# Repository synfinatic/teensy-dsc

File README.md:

# TeensyDSC: WiFi enabled Digital Setting Circles

## Important Note

As of Nov 16, 2014 I've been able to order a PCB from OSHPark using the 
[Simple-DSC](https://github.com/synfinatic/teensy-dsc/tree/simple-dsc/eagle)
design and with the latest code from 
[master](https://github.com/synfinatic/teensy-dsc/commit/1c4c6b0b567ba3cc21cd7ba83029384eee6130e7).
I seem to have a working solution using SkySafari Pro on my iPad with 
[US Digital S2-2500](http://www.usdigital.com/products/encoders/incremental/rotary/shaft/S2)
10,000 step optical encoders.

For more information, please see the [TeensyDSC Wiki](https://github.com/synfinatic/teensy-dsc/wiki)

There is also this thread on [CloudyNights](http://www.cloudynights.com/topic/482436-yet-another-diy-digital-setting-circles-project-teensydsc/)

## Basic Features
I wanted to do my own digital setting circles (DSC) for my 
[Apertura AD12](http://www.opticsmart.com/telescopes/dobsonian-telescopes/apertura-ad12-dobsonian-reflector-telescope.html).
The main goals were:

 * Tested to support 40,000 resolution via quadurature decoding using [US Digital S2-10000-250-IE-D-D encoders](http://usdigital.com/products/encoders/incremental/rotary/shaft/S2)
 * Should support resolutions in excess of 100K
 * Built in WiFi access point to allow wirelessly interfacing to an Apple iPad or Android tablet
 * Supporting at least [SkySafari Plus/Pro](http://www.skysafariastronomy.com/)
 * Powered via USB connection or external 7-24V battery source
 * Using industry standard RJ45 connection to encoders
 * Open source software & PCB design (GPLv3)
    * PCB Design done in [Eagle PCB](http://www.cadsoftusa.com/eagle-pcb-design-software/?language=en)
    * PCB's available from [OshPark](http://www.oshpark.com)
 * Small 2"x3"x1" enclosure
 * Inexpensive!  All the components should be available for < $100.

That will be version 1.0.  Future versions will hopefully support other features,
but for now that will be enough for it to work for me.

## Why Teensy 3.1
Why the [Teensy 3.1](http://pjrc.com/store/teensy31.html) and not Arduino?

 * It is *much* faster then the Arduino Uno or Mega (32bit 72Mhz CPU vs 16bit 16Mhz)
 * Small footprint and only costs $20!
 * Runs at 3.3V, but handles 5V just fine which simplifies talking to WiFi chipsets and encoders
 * It supports interrupts on all digital pins which allows for higher resolution encoders
 * Has 3 hardware serial ports which allows interfacing with GoTo hardware, etc
 * More memory & flash allows for a lot more features

## Required Libraries & Software
TeensyDSC requires some additional Arduino libraries to compile/run:

 * [Arduino IDE v1.6.x](http://arduino.cc/en/Main/Software)
 * [Teensyduino](http://pjrc.com/teensy/td_download.html) - Teensy addon for the Arduino IDE

The following libraries are included with the TeensyDSC source code, but you
will need to import them into the Arduino IDE:

 * [AnySerial](https://github.com/synfinatic/AnySerial) - Serial port abstraction layer for Arduino
 * [WiFi_Shield](https://github.com/synfinatic/WiFi_Shield) - Customized to use AnySerial
 * [Flash](https://github.com/mikalhart/Flash) - Easy access to EEPROM flash memory

## Supported DSC Software
Please note that I have limited access to software, so this may not be a
complete list.  If you have tested TeensyDSC with some software, I'd love
to hear if it worked or not.  If it did not work, hopefully we can work
together to make it work!

 * SkySafari (OSX, iOS)  
   * Scope Type: Basic Encoder System
   * For "Encoder Steps per Revolution" click "Get Automatically"

## Similar Projects
There are a bunch of similar projects to TeensyDSC which you should be aware of:

 * [mrosseel/arduino-dsc](https://github.com/mrosseel/arduino-dsc)
 * [mdw123/arduino-dsc](https://github.com/mdw123/arduino-dsc)
 * [Arduino Bluetooth DSC](http://orlygoingthirty.blogspot.com/2012/01/arduino-bluetooth-digital-setting.html)
 * [Mike Fulbright's Arduino DSC](http://msfastro.net/articles/arduinodsc/)

## Similar Commercial Products
There are two commercial products which shares many of the same features of TeensyDSC:

 * [Astro Devices Nexus](http://www.astrodevices.com/products/Nexus/Nexus.html)
 * [Dave Ek's Setting Circles](http://eksfiles.net/digital-setting-circles/)

## DSC to WiFi adapters
These commercial products connect your DSC adapter (Sky Commander, etc) to Sky Safari:

 * [Southern Stars/Orion SkyFi](http://www.southernstars.com/products/skyfi/)
 * [Astro Devices Nexus-S](http://www.astrodevices.com/products/NexusS/NexusS.html)

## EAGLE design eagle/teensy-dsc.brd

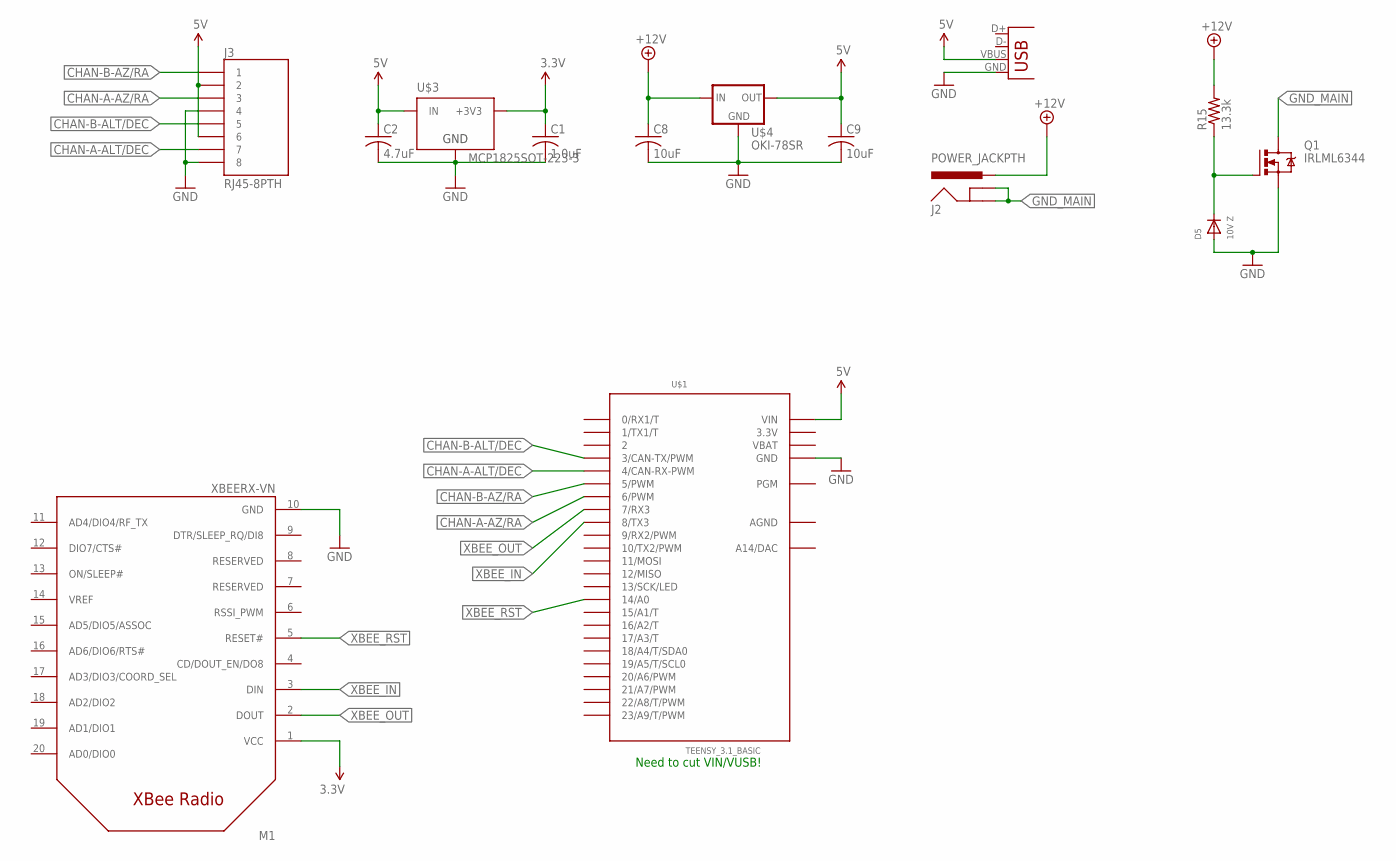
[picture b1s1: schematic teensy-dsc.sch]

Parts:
C1: 1.0uF; C0805
C2: 4.7uF; C0805
C8, C9: 10uF; C0805
D5: 10V Z; SOD-123
J1: USB-B; USB-B-PTH
J2: POWER_JACKPTH; POWER_JACK_PTH
J3: RJ45-8PTH; RJ45-8
M1: XBEERX-VN; RX-VN
Q1: IRLML6344; SOT23
R15: 13.3k; M0805
U$1: TEENSY_3.1_BASIC
U$3: MCP1825SOT-223-3; SOT-223
U$4: OKI-78SR; OKI-78SR-H

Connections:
3.3V: C1.1, M1.1 (VCC), U$3.3 (+3V3)
5V: C2.1, C9.1, J1.VBUS, J3.2, J3.6, U$1.VIN, U$3.1 (IN), U$4.P$3 (OUT)
+12V: C8.1, J2.PWR, R15.2, U$4.P$1 (IN)
AGND: U$1.AGND
CHAN-A-ALT/DEC: J3.7, U$1.4 (4/CAN-RX-PWM)
CHAN-A-AZ/RA: J3.3, U$1.6 (6/PWM)
CHAN-B-ALT/DEC: J3.5, U$1.3 (3/CAN-TX/PWM)
CHAN-B-AZ/RA: J3.1, U$1.5 (5/PWM)
GND: C1.2, C2.2, C8.2, C9.2, D5.A, J1.GND, J3.4, J3.8, M1.10 (GND), Q1.2 (S), U$1.GND, U$1.GND1 (GND), U$3.2 (GND), U$4.P$2 (GND)
GND_MAIN: J2.GND, J2.GNDBREAK, Q1.3 (D)
unnamed: D5.C, Q1.1 (G), R15.1
XBEE_IN: M1.3 (DIN), U$1.8 (8/TX3)
XBEE_OUT: M1.2 (DOUT), U$1.7 (7/RX3)
XBEE_RST: M1.5 (RESET#), U$1.14/A0

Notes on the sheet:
Need to cut VIN/VUSB!

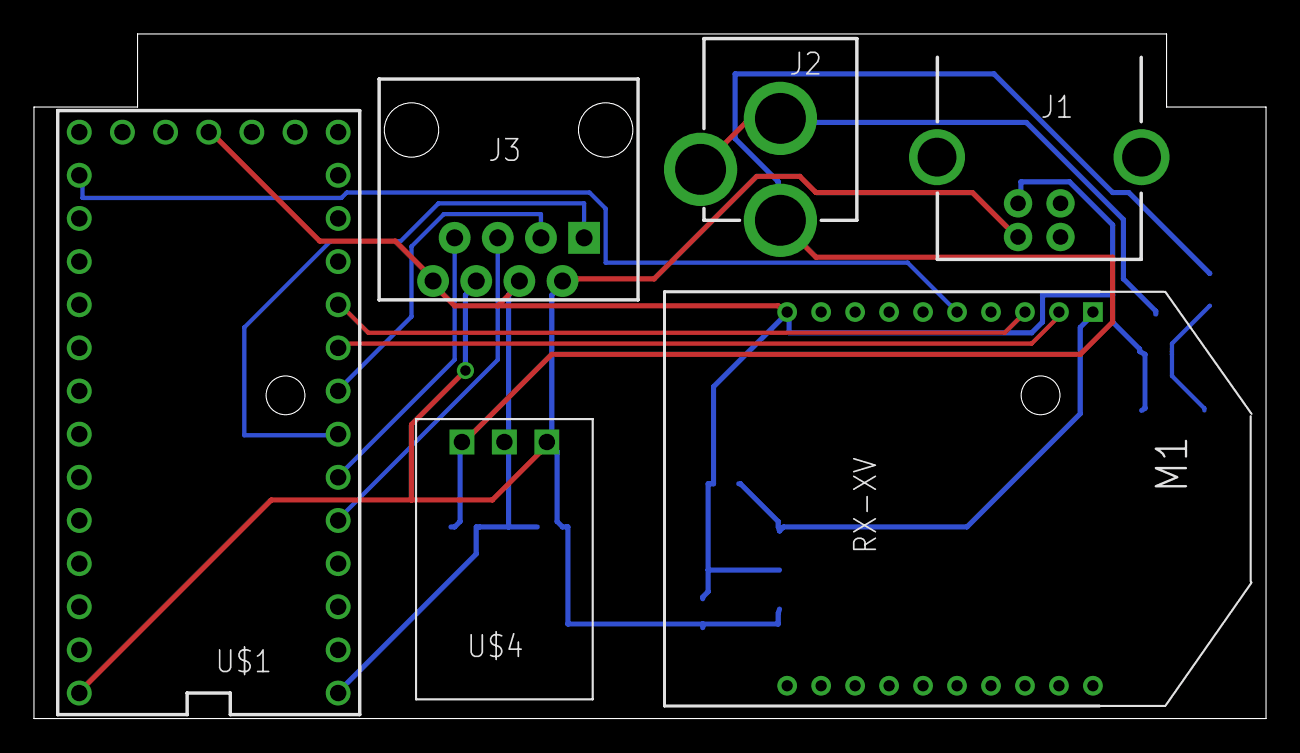
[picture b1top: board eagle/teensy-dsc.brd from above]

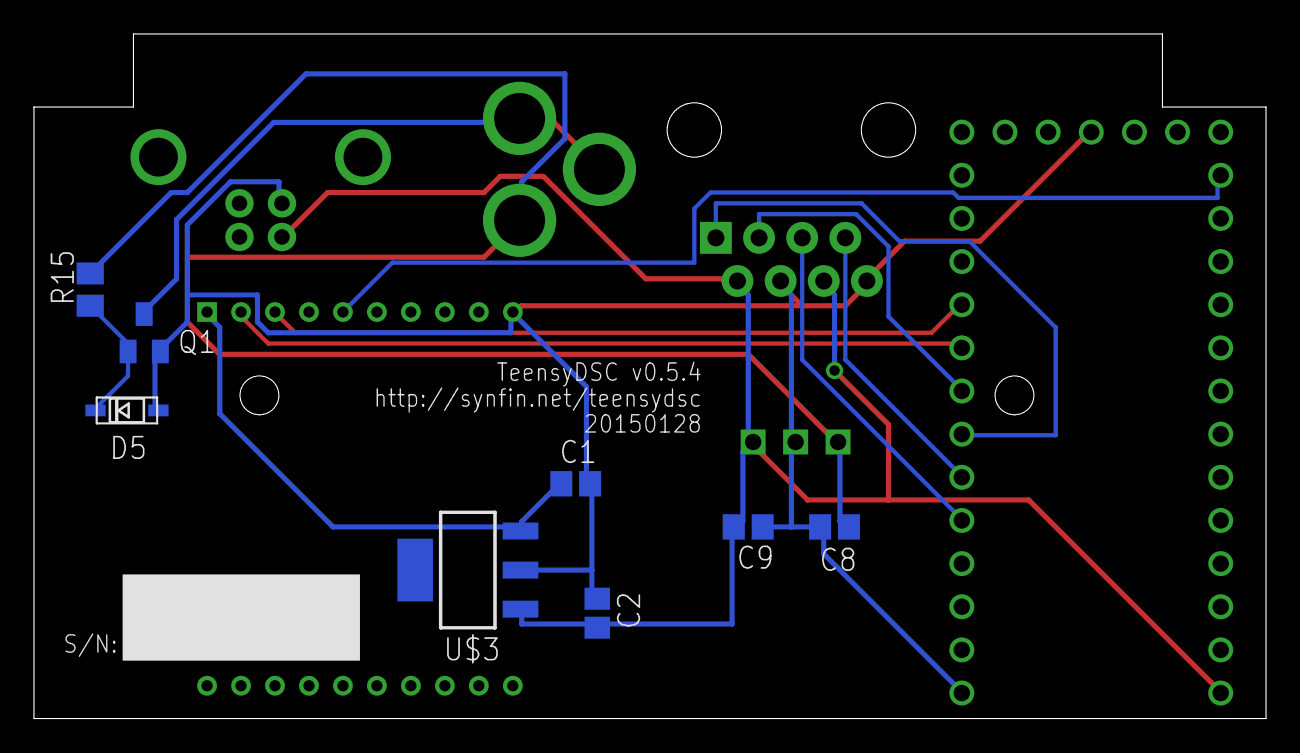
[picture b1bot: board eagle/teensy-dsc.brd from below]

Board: 2 copper layers, 72.5 x 40.3 mm, 14 parts (8 on the bottom side), 13 nets.

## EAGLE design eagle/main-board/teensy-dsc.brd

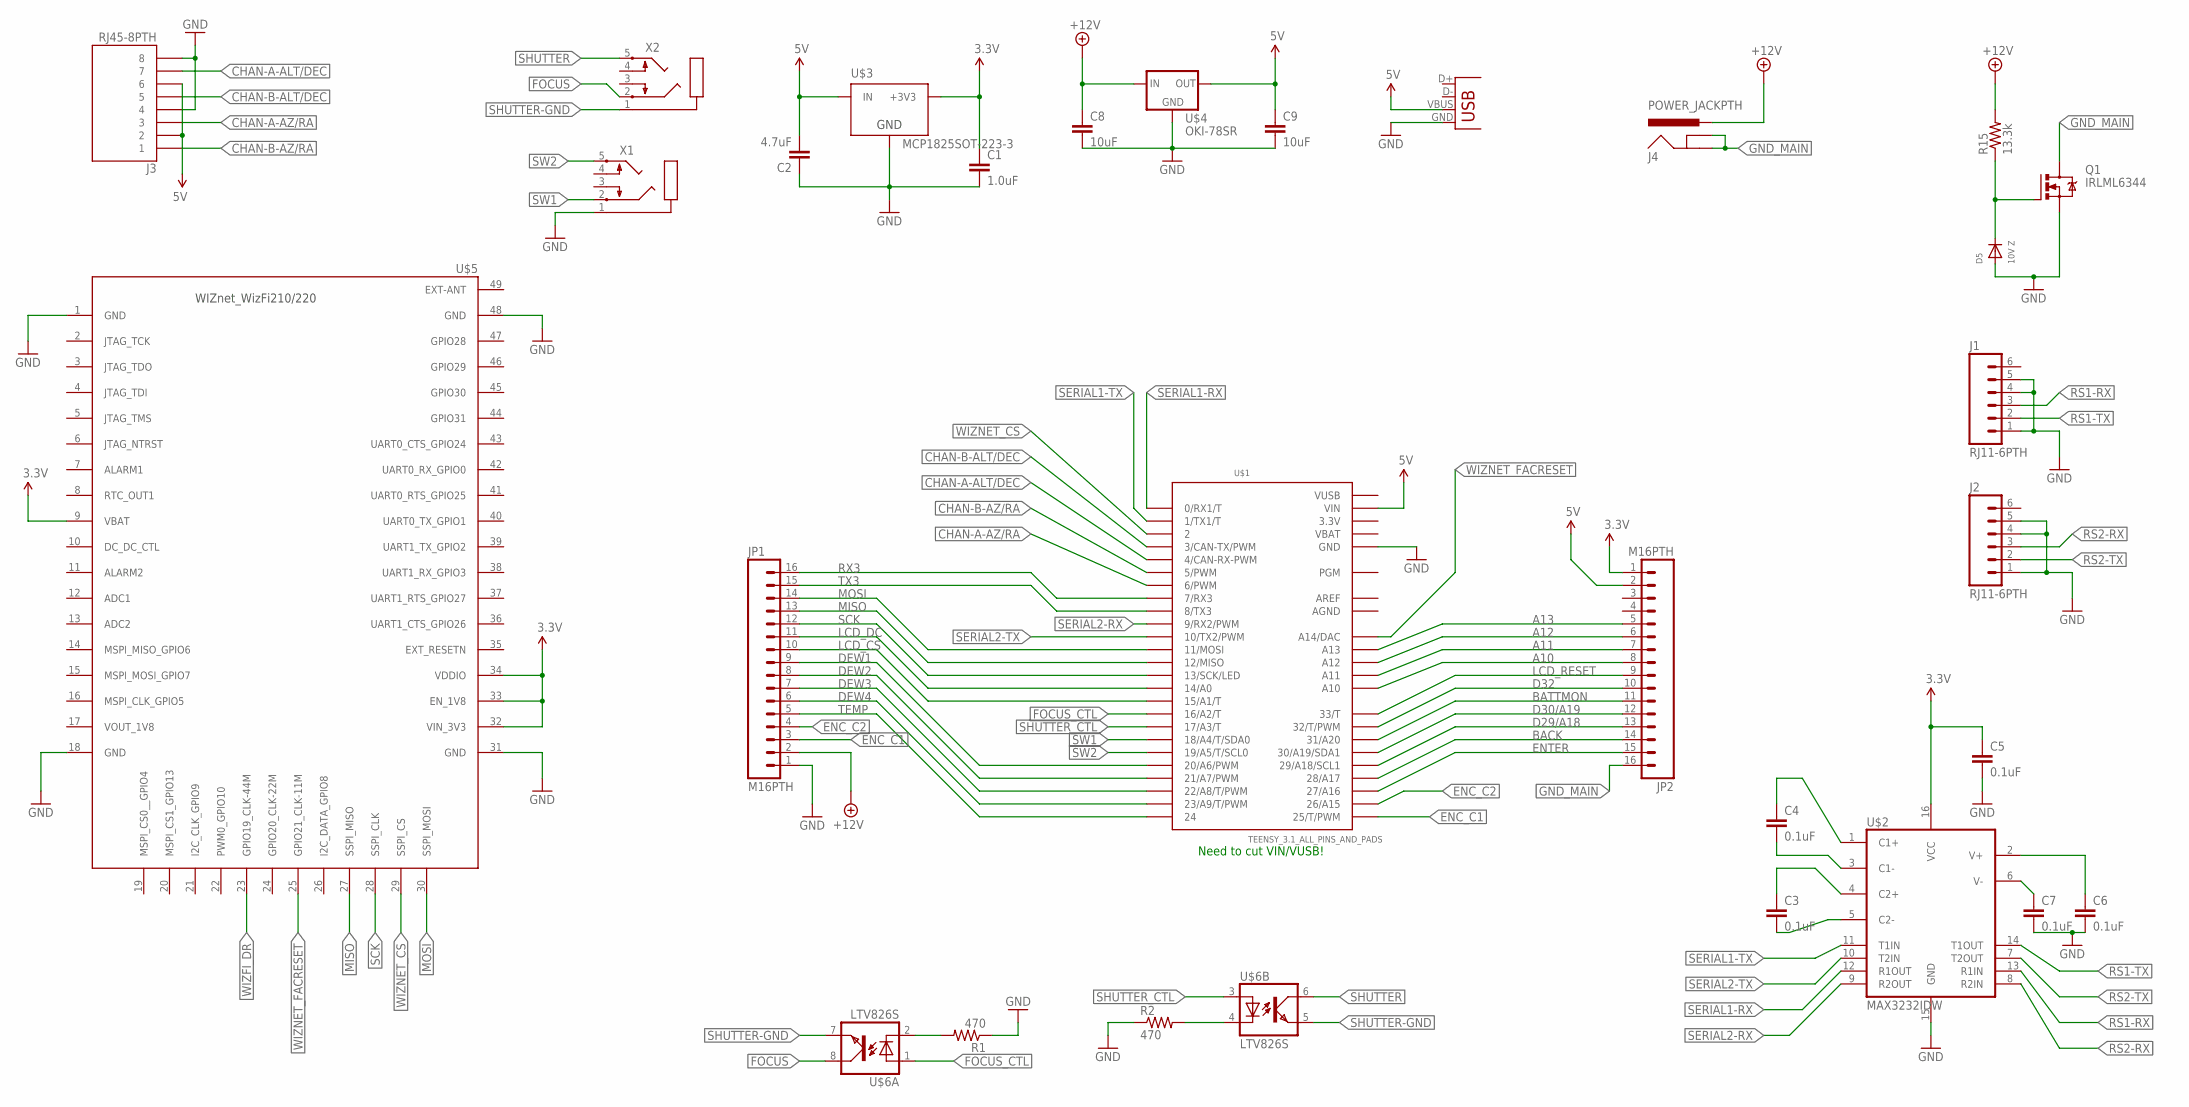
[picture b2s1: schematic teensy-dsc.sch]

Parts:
C1: 1.0uF; C0805
C2: 4.7uF; C0805
C3, C4, C5, C6, C7: 0.1uF; C0805
C8, C9: 10uF; C0805
D5: 10V Z; SOD-123
J1, J2: RJ11-6PTH; RJ11-6
J3: RJ45-8PTH; RJ45-8
J4: POWER_JACKPTH; POWER_JACK_PTH
J5: USB-B; USB-B-PTH
JP1, JP2: M16PTH; 1X16
Q1: IRLML6344; SOT23
R1, R2: 470; M0805
R15: 13.3k; M0805
U$1: TEENSY_3.1_ALL_PINS_AND_PADS; TEENSY_3.1_ALLPINS
U$2: MAX3232IDW; SO016
U$3: MCP1825SOT-223-3; SOT-223
U$4: OKI-78SR; OKI-78SR-H
U$5: WIZFI210/220
U$6: LTV826S; DIL8-SMD
X1, X2: STEREOJACK; STX3100

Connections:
3.3V: C1.1, C5.1, JP2.1, U$1.3.3V, U$1.3.3V1 (3.3V), U$1.3.3V2 (3.3V), U$2.16 (VCC), U$3.3 (+3V3), U$5.9 (VBAT), U$5.32 (VIN_3V3), U$5.33 (EN_1V8), U$5.34 (VDDIO)
5V: C2.2, C9.1, J3.2, J3.6, J5.VBUS, JP2.2, U$1.VIN, U$3.1 (IN), U$4.P$3 (OUT)
+12V: C8.1, J4.PWR, JP1.2, R15.2, U$4.P$1 (IN)
A10: JP2.8, U$1.A10
A11: JP2.7, U$1.A11
A12: JP2.6, U$1.A12
A13: JP2.5, U$1.A13
AGND: U$1.AGND
AREF: U$1.AREF
BACK: JP2.14, U$1.28 (28/A17)
BATTMON: JP2.11, U$1.31 (31/A20)
CHAN-A-ALT/DEC: J3.7, U$1.4 (4/CAN-RX-PWM)
CHAN-A-AZ/RA: J3.3, U$1.6 (6/PWM)
CHAN-B-ALT/DEC: J3.5, U$1.3 (3/CAN-TX/PWM)
CHAN-B-AZ/RA: J3.1, U$1.5 (5/PWM)
D29/A18: JP2.13, U$1.29 (29/A18/SCL1)
D30/A19: JP2.12, U$1.30 (30/A19/SDA1)
D32: JP2.10, U$1.32 (32/T/PWM)
DEW1: JP1.9, U$1.20/A6 (20/A6/PWM)
DEW2: JP1.8, U$1.21/A7 (21/A7/PWM)
DEW3: JP1.7, U$1.22/A8 (22/A8/T/PWM)
DEW4: JP1.6, U$1.23/A9 (23/A9/T/PWM)
ENC_C1: JP1.3, U$1.25 (25/T/PWM)
ENC_C2: JP1.4, U$1.26 (26/A15)
ENTER: JP2.15, U$1.27 (27/A16)
FOCUS: U$6.8 (COL), X2.2
FOCUS_CTL: U$1.16/A2 (16/A2/T), U$6.1 (A)
GND: C1.2, C2.1, C5.2, C6.2, C7.2, C8.2, C9.2, D5.A, J1.1, J1.4, J1.5, J2.1, J2.4, J2.5, J3.4, J3.8, J5.GND, JP1.1, Q1.2 (S), R1.1, R2.1, U$1.GND, U$1.GND1 (GND), U$1.GND2 (GND), U$2.15 (GND), U$3.2 (GND), U$4.P$2 (GND), U$5.1 (GND), U$5.18 (GND), U$5.31 (GND), U$5.48 (GND), X1.1
GND_MAIN: J4.GND, J4.GNDBREAK, JP2.16, Q1.3 (D)
LCD_CS: JP1.10, U$1.15/A1 (15/A1/T)
LCD_DC: JP1.11, U$1.14/A0
LCD_RESET: JP2.9, U$1.33 (33/T)
MISO: JP1.13, U$1.12 (12/MISO), U$5.27 (SSPI_MISO)
MOSI: JP1.14, U$1.11 (11/MOSI), U$5.30 (SSPI_MOSI)
unnamed: C4.1, U$2.1 (C1+)
unnamed: C4.2, U$2.3 (C1-)
unnamed: C3.1, U$2.4 (C2+)
unnamed: C3.2, U$2.5 (C2-)
unnamed: C7.1, U$2.6 (V-)
unnamed: C6.1, U$2.2 (V+)
unnamed: R2.2, U$6.4 (C)
unnamed: R1.2, U$6.2 (C)
unnamed: D5.C, Q1.1 (G), R15.1
RS1-RX: J1.3, U$2.13 (R1IN)
RS1-TX: J1.2, U$2.14 (T1OUT)
RS2-RX: J2.3, U$2.8 (R2IN)
RS2-TX: J2.2, U$2.7 (T2OUT)
RX3: JP1.16, U$1.7 (7/RX3)
SCK: JP1.12, U$1.13 (13/SCK/LED), U$5.28 (SSPI_CLK)
SERIAL1-RX: U$1.0 (0/RX1/T), U$2.12 (R1OUT)
SERIAL1-TX: U$1.1 (1/TX1/T), U$2.11 (T1IN)
SERIAL2-RX: U$1.9 (9/RX2/PWM), U$2.9 (R2OUT)
SERIAL2-TX: U$1.10 (10/TX2/PWM), U$2.10 (T2IN)
SHUTTER: U$6.6 (COL), X2.5
SHUTTER-GND: U$6.5 (EMIT), U$6.7 (EMIT), X2.1
SHUTTER_CTL: U$1.17/A3 (17/A3/T), U$6.3 (A)
SW1: U$1.18/A4 (18/A4/T/SDA0), X1.2
SW2: U$1.19/A5 (19/A5/T/SCL0), X1.5
TEMP: JP1.5, U$1.24
TX3: JP1.15, U$1.8 (8/TX3)
VBAT: U$1.VBAT
VUSB: U$1.VUSB
WIZFI_DR: U$5.23 (GPIO19_CLK-44M)
WIZNET_CS: U$1.2, U$5.29 (SSPI_CS)
WIZNET_FACRESET: U$1.A14 (A14/DAC), U$5.25 (GPIO21_CLK-11M)

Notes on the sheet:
Need to cut VIN/VUSB!

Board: 2 copper layers, 29 parts (17 on the bottom side), 60 nets, no tracks yet.

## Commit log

2013-07-21 .gitignore
2013-07-27 update to work with iOS-based apps
2013-07-27 tweak for release
2014-09-08 First pass at a working board Teensy DSC
    - Power via USB cable
    - DSC uses same RJ45 pintout as AstroDevices Nexus
    - Uses Teensy 3.1 & any valid Xbee module!
2014-09-08 updated with:
    - latest WiFly board
    - Thicker traces for routing 5V & GND
    - Removed wiring for 3.3V on Teensy 3.1 board
2014-09-09 New board design: - Add 2x serial ports - Add camera trigger (opto-isolated) - Add 2x external button/switch - Add dedicated program button Remove old PCB design files Start work on TeensyDSC code
2014-09-09 Mark board v0.2 Add a warning so people don't think it's ready for prime-time.
2014-09-10 ignore Eagle .job files
2014-09-10 update README & don't track the Eagle .pro files
2014-09-10 Update board design with: - Remove program button since USB host mode isn't supported - Add 5mm barrel connector for ~12V power - Add necessary reverse polarity protection & regulation for 12V power 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
2014-09-11 We don't need digitalWriteFast on the Teensy
2014-09-12 commit changes prior to renaming
2014-09-12 rename directory/files so Arduino app will open them- doesn't like dashes in file name :-/
2014-09-13 Fix power error in .sch Update board to theoretically fit in CU-789 box
2014-09-13 fix labels on board
2014-09-14 sync up with latest board change v0.4
2014-09-14 Lots of bug changes. teensy_dsc.ino currently uses AnySerial
2014-09-14 save WiFlySerial using AnySerial using polymorph
2014-09-14 code actually compiles
2014-09-14 fix compile time warnings
2014-09-14 re-indent
2014-09-14 Add support for SoftwareSerial (aka NewSoftSerial) Add support for print/printf/etc to AnySerial update teensy_dsc & wifly to use updated AnySerial code
2014-09-14 update license to GPLv3 update copyright statements update our basic documentation
2014-09-14 remove AnySerial & WiFlySerial from our repo since they're now independant projects on GitHub
2014-09-14 remove unneeded code & small cleanup for teensy_dsc
2014-09-15 Lots of changes:
    - Start working on a CLI framework
    - Update Commands & Readme docs
    - Note on the Eagle file that we need to cut the VUSB/VIN pads apart
    - Re-organize some header files
    - general cleanup
2014-09-15 update readme with more info
2014-09-15 lots of work on the CLI. Maybe I should test this. :)
2014-09-16 we use the Flash library too
2014-09-16 add get_dsc_resolution and clean up cli code a bit
2014-09-16 rework inital WiFly setup
    - put static strings in Flash
    - clean up constants
2014-09-20 lots of changes:
    - Defaults are now written to EEPROM
    - Config params are passed into WiFlySerial via API rather the CLI
    - CLI now handles it's own context
    - Much better error handling in CLI
    - use MsTimer2 to update encoders
2014-09-20 Try to document our commands and improve our list of libraries and other misc notes
2014-09-20 sync eagle changes
2014-09-20 Basic CLI encoder reading & setting of resolution seems to be working
    Still need to apply resolution some how??
2014-09-20 now version 0.2\r
2014-09-21 We need a specific version of MsTimer2
2014-09-21 use the original Flash library
2014-09-22 extend CLI a lot and add support for WiFi
    - saving network/etc options to EEPROM now works
    - reading from EEPROM works
    - Some WiFi config works (SSID does NOT work??)
    - Enabling AP mode does not work (hangs)
    - remove a lot of unneeded debug statements
    - WiFi interactive (talking directly with WiFly board) works
2014-11-02 small tweaks I want to save
2014-11-03 v0.5 simple board/just DSC functionality
    No serial, camera, etc.
    Has USB & 12V power input options
2014-11-03 move xbee reset pin to 14 to match schematic
2014-11-17 Orion Intelliscope mode with SkySafari Pro 4.0 works!
    - Tested AP mode
    - Able to configure WiFly board & save settings
    - Switched from WiFlySerial to WiFly library
2014-11-17 Update readme with latest info.
2014-11-17 Small improvements to simple board v0.5.1:
    - Move RJ45 up to be flush with USB
    - Move cap labels to be readable
2014-11-18 stop tracking the eagle.epf file
2014-11-18 link to the wiki for building your own
2014-11-18 step not clicks
2014-11-19 link to wiki
2014-11-19 don't track eagle/eagle.epf
2014-11-19 link to CN thread
2014-11-19 small tweaks to the readme
2014-11-21 small updates to the readme
2014-11-21 Start v0.9 board design
    - Has two 1x16 headers for expansion boards
    - 85x55mm design
    - four mounting holes
    - ports on two sides
2014-11-21 approve DRU rule check
2014-11-22 move teensy-dsc design to main-board
    Last design with WiFly board
2014-11-22 ignore *.b## files
2014-11-22 Initial WizFi210/220 redesign
    Also fixes naming of various Teensy pins which were wrong
    or incorrectly routed for serial ports/shutter/focus per
    the Google doc.
2014-11-22 start work on dew-heater board & remove root dir DESCRIPTION
2014-11-23 more WizFi updates....
    After further research, I'm not convinced the WizFi is the way to go.
    Most likely will need to replace it with something else if I want
    to support serial ports. Probably should move the serial ports
    to a daughter board.
2014-11-24 update component labels on PCB to be easier to read
2014-11-25 Massive fixes to EEPROM defaults saving & loading.
    Reflashing always zeros out the EEPROM. We now load
    our defaults from defaults.h if needed. Once you change
    the config, call SAVE and they'll be stored in the EEPROM
    until the next time you reflash the code.
    Most if not all the config options are now properly set & read.
2014-11-25 rename network.[h|ino] to be rnxv.[h|ino] and clean up code
    removed a lot of unused functions
    renamed functions to be rnxv_*
2014-11-26 stop using MsTimer2 to update encoders, just read as needed
2014-11-26 move printf strings to flash via F()
2014-11-27 fix MODE WIFI mode
    Less confusing now. Auto passes '$$$' to the WiFly and 'exit\r'
    when we change modes.
    refs #28
2014-11-27 reintroduce LED blinking to indicate all is OK
    During startup, the LED is solid on and starts blinking
    once we're ready
2014-12-02 disable AP link monitor and enable webserver
2015-01-01 update date on brd to be a valid date update version on sch to match the brd
2015-01-06 trim board a little to better fit in the enclosure
2015-01-18 fix some bugs with the CLI:
    - Not saving encoder values in EEPROM
    - Can't switch to AP mode
    - Memory is reused w/o zero'd out
2015-01-19 add S2 Adapter breakout board v1.0
2015-01-19 Add a short readme about the S2 adapter board
2015-01-28 Increase size of holes for OKI power module: v0.5.4
    OEM pins on the OKI module are larger then most and wont fit.
    Rev board to v0.5.4
    fixes #32
2015-01-29 fix setting AP SSID on WiFly
2015-02-04 remove compile warnings
2015-02-04 fix compile warnings and some small bugs
2015-03-20 add support for BBox Z, H and P cli commands fix compile warnings
    fixes #34
2015-03-23 fix "P" DSC command from erroring out
2015-04-09 update readme with latest info on SkySafari modes and Arduino software version
2015-04-25 Ticket #39: Fix encoder readout
    Change code to match the spec as provided by the MicroGuider.
    We now wrap between +/- half resolution for resolution <= 2^16
    or 0->resolution-1 for higher resolutions.
2015-05-01 first pass at adding some unit tests.
    many tests fail, but at least I have something to work with.
2015-05-06 Fix #39: Fix ngc_convert_encoder_value()
    Unit tests seem to work and cover all our corner cases
    Update teensy_dsc code to use fixed method
    Still, wish I didn't have to duplicate the code. :-/
2015-05-07 ticket #40: Add test mode
    Press T to toggle between test mode on & off.
    Right now it's hard coded to print every 100ms.
2015-05-08 fix link to WiFi library
2015-05-08 add simple test.py script for testing TeensyDSC
2015-05-08 fixes #42: alignment support
    adds support for the A and a commands to track alignment
2015-05-08 make test.py script executable
2015-05-09 Improve test.py script a lot
2015-05-09 clean up test.py
2015-05-09 update test.py
    - print stats on Ctrl-C
    - count number of times we exceed warning level (default 0.3sec)
    - be more accurate on calc avg based on actual run time
2015-05-10 Update COMMANDS.md & clean up cli.cpp
    - Add/fix missing commands
    - Optimize cli commands a little
2015-05-10 refs: #41 include all the libraries we need.
    This doesn't currently auto-import them into the Arduino.app
    or anything like that (you still need to manually import them)
    but at least you don't have to go looking for them & download
    them one by one.
2015-05-10 Improve test.py
    - Clean up code to be more readable
    - Show defaults with -h
    - --verbose can now be called twice for more verbosity
2015-05-11 add support for testing via Serial/USB & improve output of test.py script
2015-05-12 refactor code to make it easier to unit test
    - move key method to it's own dsc.[h|ino]
    - remove same method from unit_tests.ino
    - Makefile to copy necessary files
    Use Arduino tool to compile/run unit tests
2015-05-14 update readme for libraries
2015-05-14 Teensyduino includes the MsTimer2 library
2015-05-14 Set the copyright & license clause on every source file
2015-05-24 switch Flash to use my fork
2015-05-24 Update with pull request to fix Arduino 1.5.x support
    https://github.com/mikalhart/Flash/pull/5
2015-05-24 remove all library submodules
2015-05-24 redo libraries because I apparently fucked up
2015-05-24 Remove dependency on Streaming.h
2015-09-20 Only the AstroDevices Nexus is really similar to the TeensyDSC
2017-06-30 Fix negative encoder range
    So if you install your encoder on the "other" side, you need
    to configure it as a negative resolution. The old code handled
    this very badly and effectively returned really bad results if
    you configured a negative resolution.
    We also write a bunch of unit tests to validate the values are now
    correct.
2017-07-04 Fix negative resolution support
    Negative resolution was totally broken! Fix support and write a
    bunch of test cases proving it works.
    One little problem... the negative 10K tests don't work reliably??? WTF?
    They work just fine on their own, but don't work when other tests are
    run. No idea why?
    Fixes #46
2017-07-09 Don't double negative
    So when an encoder resolution is negative, I was reversing the
    result returned to the DSC. This is *WRONG*. The DSC is supposed to
    do the needful when the resolution is negative. This caused a problem
    (usually for Alt encoders) whereby up was down and down was up when the
    resolution is negative.
    We now cacluate the value to return to the DSC the same regardless of
2018-05-02 replace bzero with memset
    fixes compile under Arduino IDE 1.8.5

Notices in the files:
parts and their libraries:
SparkFun-Connectors: Licensing: Creative Commons ShareAlike 4.0 International - https://creativecommons.org/licenses/by-sa/4.0
SparkFun: Licensing: CC v3.0 Share-Alike You are welcome to use this library for commercial purposes.
